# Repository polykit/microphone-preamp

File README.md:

# Microphone preamp with phantom power

This repository contains schematics and PCB of a microphone preamp with switchable phantom power. It is based on the INA217 low-noise instrumentation amplifier. An additional buck-boost converter is needed for a phantom power higher than 12V. 

## BOM

|Reference      |Quantity|Value           |Note                           |
|---------------|--------|----------------|-------------------------------|
|C1 C3 C6 C7 C8 |5       |100n            |Ceramic caps                   |
|C9 C10         |2       |10u             |                               |
|C2             |1       |47u/50          |                               |
|C4 C5          |2       |47u/50**        |Bipolar caps                   |
|D1 D2 D3 D4    |4       |1N4148          |                               |
|J1             |1       |LED             |Molex KK 2.54mm 2-pin connector|
|J2             |1       |PHANTOM POWER   |Molex KK 2.54mm 3-pin connector|
|J3             |1       |MIC XLR         |Molex KK 2.54mm 3-pin connector|
|J4             |1       |PHANTOM POWER SW|Molex KK 2.54mm 3-pin connector|
|J5             |1       |GAIN 10k        |Molex KK 2.54mm 2-pin connector|
|J6             |1       |OUT             |Molex KK 2.54mm 2-pin connector|
|J7             |1       |POWER           |10-pin IDC connector           |
|R1             |1       |10k*            |                               |
|R10 R11        |2       |10              |                               |
|R2 R3          |2       |6k8             |                               |
|R4             |1       |47k             |                               |
|R5 R6          |2       |2k2             |                               |
|R7             |1       |100***          |                               |
|R8             |1       |1M              |                               |
|R9             |1       |1k              |                               |
|U1             |1       |INA217          |DIP-8 package                  |
|U2             |1       |TL071           |                               |
|               |1       |XLR socket      |Microphone input socket        |
|               |1       |Output jack     |                               |
|               |1       |10k pot         |                               |
|               |1       |Switch SPDT     |ON-ON                          |
|               |1       |LED             |                               |

\* LED current limiting resistor, change value according to used phantom power, 10k is for 48V

\** use bipolar caps

\*** adjust to change max. gain, smaller is more gain

## Reference

https://www.ti.com/lit/ds/symlink/ina217.pdf

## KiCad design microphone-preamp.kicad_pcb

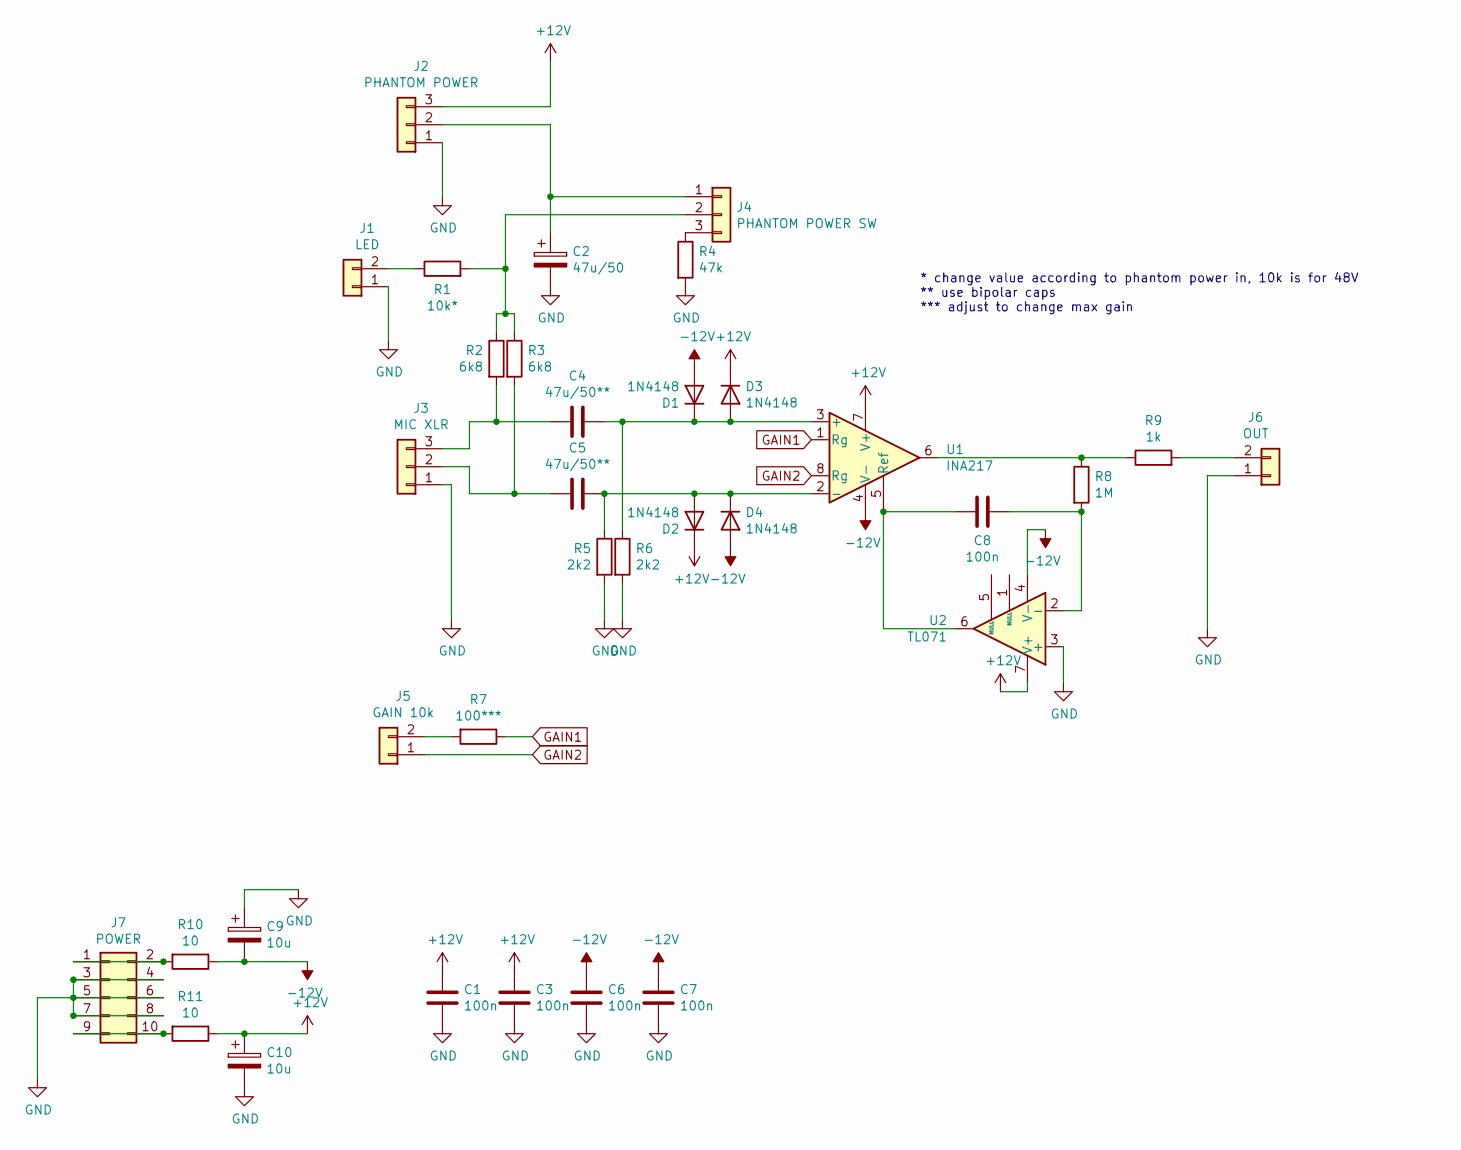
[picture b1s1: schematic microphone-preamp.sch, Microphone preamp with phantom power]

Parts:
C1, C3, C6, C7, C8: 100n; C_Disc_D3.0mm_W2.0mm_P2.50mm
C2: 47u/50; CP_Radial_D6.3mm_P2.50mm
C4, C5: 47u/50**; C_Radial_D10.0mm_H12.5mm_P5.00mm
C9, C10: 10u; CP_Radial_D5.0mm_P2.50mm
D1, D2, D3, D4: 1N4148; D_DO-35_SOD27_P7.62mm_Horizontal
J1: LED; Molex_KK-254_AE-6410-02A_1x02_P2.54mm_Vertical
J2: PHANTOM POWER; Molex_KK-254_AE-6410-03A_1x03_P2.54mm_Vertical
J3: MIC XLR; Molex_KK-254_AE-6410-03A_1x03_P2.54mm_Vertical
J4: PHANTOM POWER SW; Molex_KK-254_AE-6410-03A_1x03_P2.54mm_Vertical
J5: GAIN 10k; Molex_KK-254_AE-6410-02A_1x02_P2.54mm_Vertical
J6: OUT; Molex_KK-254_AE-6410-02A_1x02_P2.54mm_Vertical
J7: POWER; IDC-Header_2x05_P2.54mm_Vertical
R1: 10k*; R_Axial_DIN0207_L6.3mm_D2.5mm_P10.16mm_Horizontal
R2, R3: 6k8; R_Axial_DIN0207_L6.3mm_D2.5mm_P10.16mm_Horizontal
R4: 47k; R_Axial_DIN0207_L6.3mm_D2.5mm_P10.16mm_Horizontal
R5, R6: 2k2; R_Axial_DIN0207_L6.3mm_D2.5mm_P10.16mm_Horizontal
R7: 100***; R_Axial_DIN0207_L6.3mm_D2.5mm_P10.16mm_Horizontal
R8: 1M; R_Axial_DIN0207_L6.3mm_D2.5mm_P10.16mm_Horizontal
R9: 1k; R_Axial_DIN0207_L6.3mm_D2.5mm_P10.16mm_Horizontal
R10, R11: 10; R_Axial_DIN0207_L6.3mm_D2.5mm_P10.16mm_Horizontal
U1: INA217; DIP-8_W7.62mm_Socket_LongPads
U2: TL071; DIP-8_W7.62mm_Socket_LongPads

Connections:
+12V: C1.1, C3.1, C10.1, D2.1 (K), D3.1 (K), J2.3, R11.1, U1.7 (V+), U2.7 (V+)
-12V: C6.1, C7.1, C9.2, D1.2 (A), D4.2 (A), R10.1, U1.4 (V-), U2.4 (V-)
GAIN1: R7.1, U1.1 (Rg)
GAIN2: J5.1, U1.8 (Rg)
GND: C1.2, C2.2, C3.2, C6.2, C7.2, C9.1, C10.2, J1.1, J2.1, J3.1, J6.1, J7.3, J7.4, J7.5, J7.6, J7.7, J7.8, R4.2, R5.2, R6.2, U2.3 (+)
unnamed: C2.1, J2.2, J4.1
unnamed: C4.1, J3.3, R2.2
unnamed: C4.2, D1.1 (K), D3.2 (A), R6.1, U1.3 (+)
unnamed: C5.1, J3.2, R3.2
unnamed: C5.2, D2.2 (A), D4.1 (K), R5.1, U1.2 (-)
unnamed: C8.1, R8.2, U2.2 (-)
unnamed: C8.2, U1.5 (Ref), U2.6
unnamed: J1.2, R1.1
unnamed: J4.2, R1.2, R2.1, R3.1
unnamed: J4.3, R4.1
unnamed: J5.2, R7.2
unnamed: J6.2, R9.2
unnamed: J7.1, J7.2, R10.2
unnamed: J7.9, J7.10, R11.2
unnamed: R8.1, R9.1, U1.6

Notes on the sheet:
* change value according to phantom power in, 10k is for 48V ** use bipolar caps *** adjust to change max gain

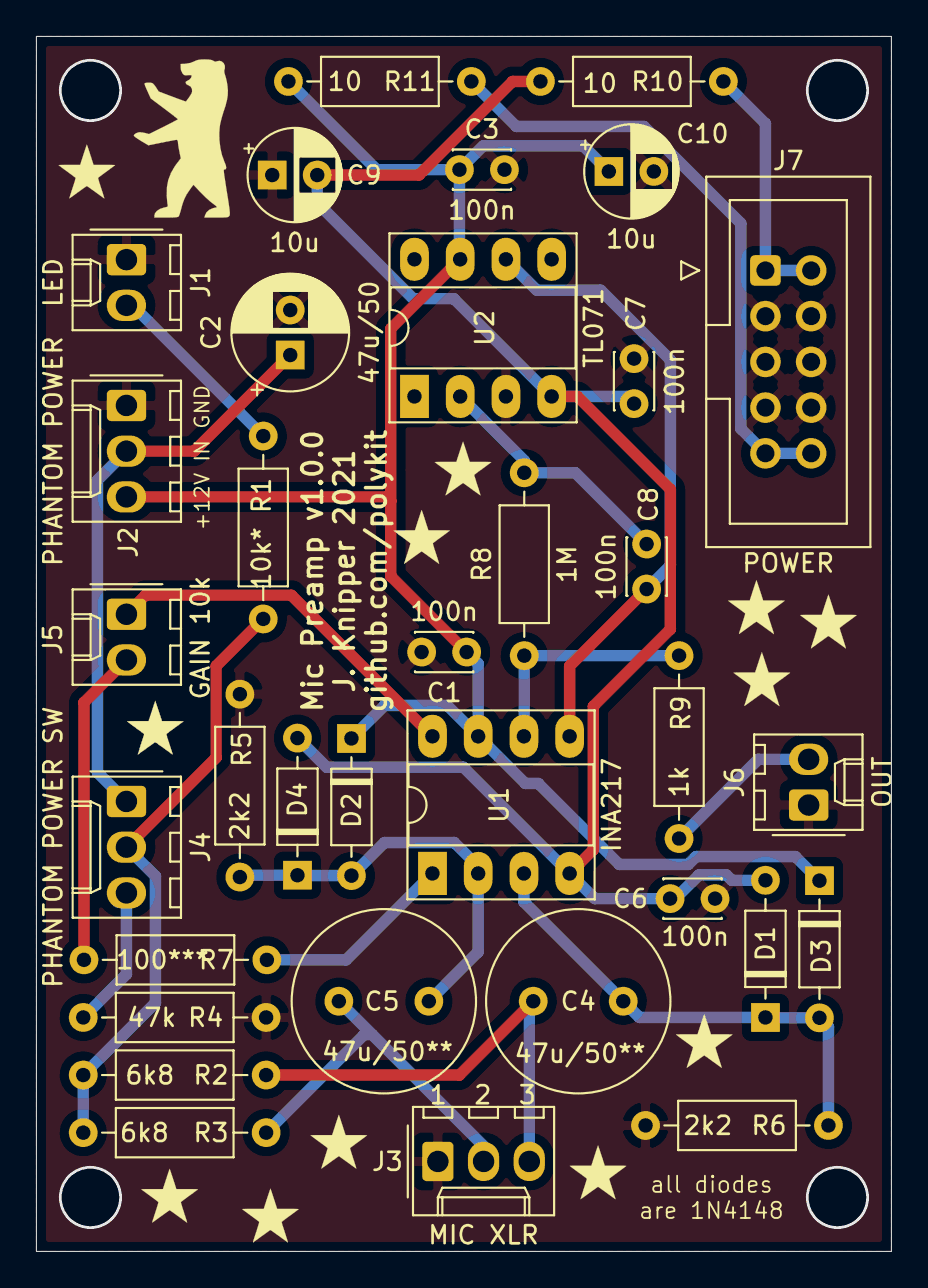
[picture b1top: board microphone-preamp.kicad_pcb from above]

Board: 2 copper layers, 47.5 x 67.5 mm, 34 parts (0 on the bottom side), 20 nets.

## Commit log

2021-09-21 Initial import
2021-09-21 Fix silkscreen, readme
